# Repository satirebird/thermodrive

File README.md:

# Thermal actuator driver for homematic HmIP-MOD-OC8

This PCB controls up to 6 thermal actuators (230VAC) using a homematic [HmIP-MOD-OC8](https://de.elv.com/elv-homematic-ip-komplettbausatz-modulplatine-opencollector-8-fach-hmip-mod-oc8-fuer-smart-home-hausautomation-150850) module. To control the actuators solid state relays with FETs are used. TRIACs are problematic due to the minimum hold current. The board fits into the DIN rail case [APRA DB6 GBK](https://www.apra.de/produkte/apra-rail-db-serie/)

Schematic, Layout and Gerber files can be used without any warranties.

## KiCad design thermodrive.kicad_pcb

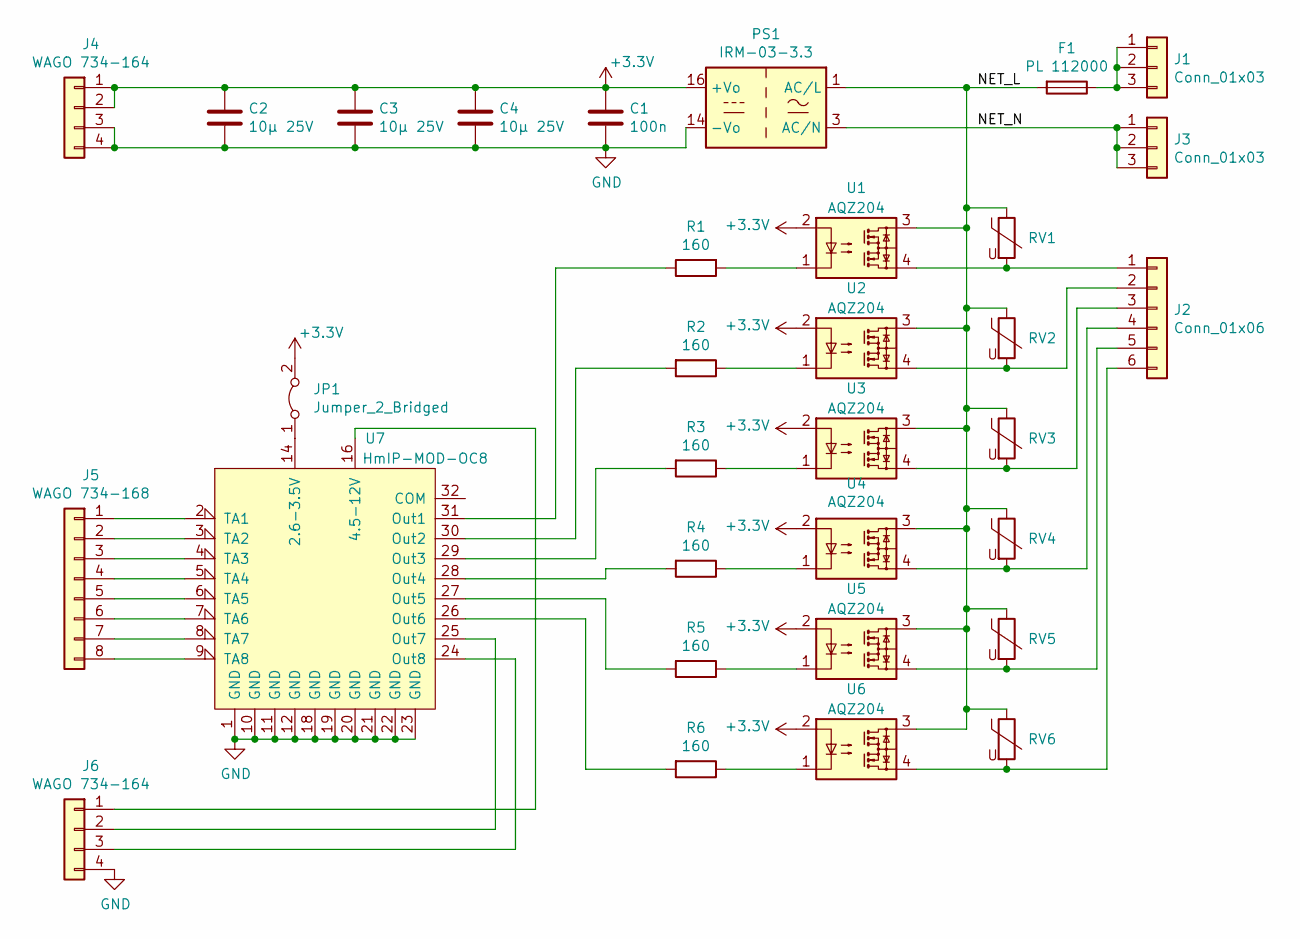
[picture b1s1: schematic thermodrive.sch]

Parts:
C1: 100n; C_0805_2012Metric
C2, C3, C4: 10µ 25V; C_1206_3216Metric
F1: PL 112000; Fuseholder5x20_horiz_SemiClosed_Casing10x25mm
J1, J3: Conn_01x03; TerminalBlock_MetzConnect_Type175_RT02703HBLC_1x03_P7.50mm_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
J2: Conn_01x06; TerminalBlock_MetzConnect_Type175_RT02706HBLC_1x06_P7.50mm_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
J4, J6: WAGO 734-164; Wago_734-164_1x04_P3.50mm_Horizontal
J5: WAGO 734-168; Wago_734-168_1x08_P3.50mm_Horizontal
JP1: Jumper_2_Bridged; PinHeader_1x02_P2.54mm_Vertical
PS1: IRM-03-3.3; Converter_ACDC_MeanWell_IRM-03-xx_THT
R1, R2, R3, R4, R5, R6: 160; R_0805_2012Metric
RV1, RV2, RV3, RV4, RV5, RV6: B72210P2271K101; RV_Disc_D12mm_W3.9mm_P7.5mm
U1, U2, U3, U4, U5, U6: AQZ204; AQZ-SIL-4
U7: HmIP-MOD-OC8

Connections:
+3V3: C1.1, C2.1, C3.1, C4.1, J4.1, J4.2, JP1.2 (B), PS1.16 (+Vo), U1.2, U2.2, U3.2, U4.2, U5.2, U6.2
/NET_L: F1.2, PS1.1 (AC/L), RV1.1, RV2.1, RV3.1, RV4.1, RV5.1, RV6.1, U1.3, U2.3, U3.3, U4.3, U5.3, U6.3
/NET_N: J3.1, J3.2, J3.3, PS1.3 (AC/N)
GND: C1.2, C2.2, C3.2, C4.2, J4.3, J4.4, J6.4, PS1.14 (-Vo), U7.1 (GND), U7.10 (GND), U7.11 (GND), U7.12 (GND), U7.18 (GND), U7.19 (GND), U7.20 (GND), U7.21 (GND), U7.22 (GND), U7.23 (GND)
unnamed: F1.1, J1.1, J1.2, J1.3
unnamed: J2.1, RV1.2, U1.4
unnamed: J2.2, RV2.2, U2.4
unnamed: J2.3, RV3.2, U3.4
unnamed: J2.4, RV4.2, U4.4
unnamed: J2.5, RV5.2, U5.4
unnamed: J2.6, RV6.2, U6.4
unnamed: J5.1, U7.2 (TA1)
unnamed: J5.2, U7.3 (TA2)
unnamed: J5.3, U7.4 (TA3)
unnamed: J5.4, U7.5 (TA4)
unnamed: J5.5, U7.6 (TA5)
unnamed: J5.6, U7.7 (TA6)
unnamed: J5.7, U7.8 (TA7)
unnamed: J5.8, U7.9 (TA8)
unnamed: J6.1, U7.16 (4.5-12V)
unnamed: J6.2, U7.25 (Out7)
unnamed: J6.3, U7.24 (Out8)
unnamed: JP1.1 (A), U7.14 (2.6-3.5V)
unnamed: R1.1, U7.31 (Out1)
unnamed: R1.2, U1.1
unnamed: R2.1, U2.1
unnamed: R2.2, U7.30 (Out2)
unnamed: R3.1, U3.1
unnamed: R3.2, U7.29 (Out3)
unnamed: R4.1, U4.1
unnamed: R4.2, U7.28 (Out4)
unnamed: R5.1, U5.1
unnamed: R5.2, U7.27 (Out5)
unnamed: R6.1, U6.1
unnamed: R6.2, U7.26 (Out6)

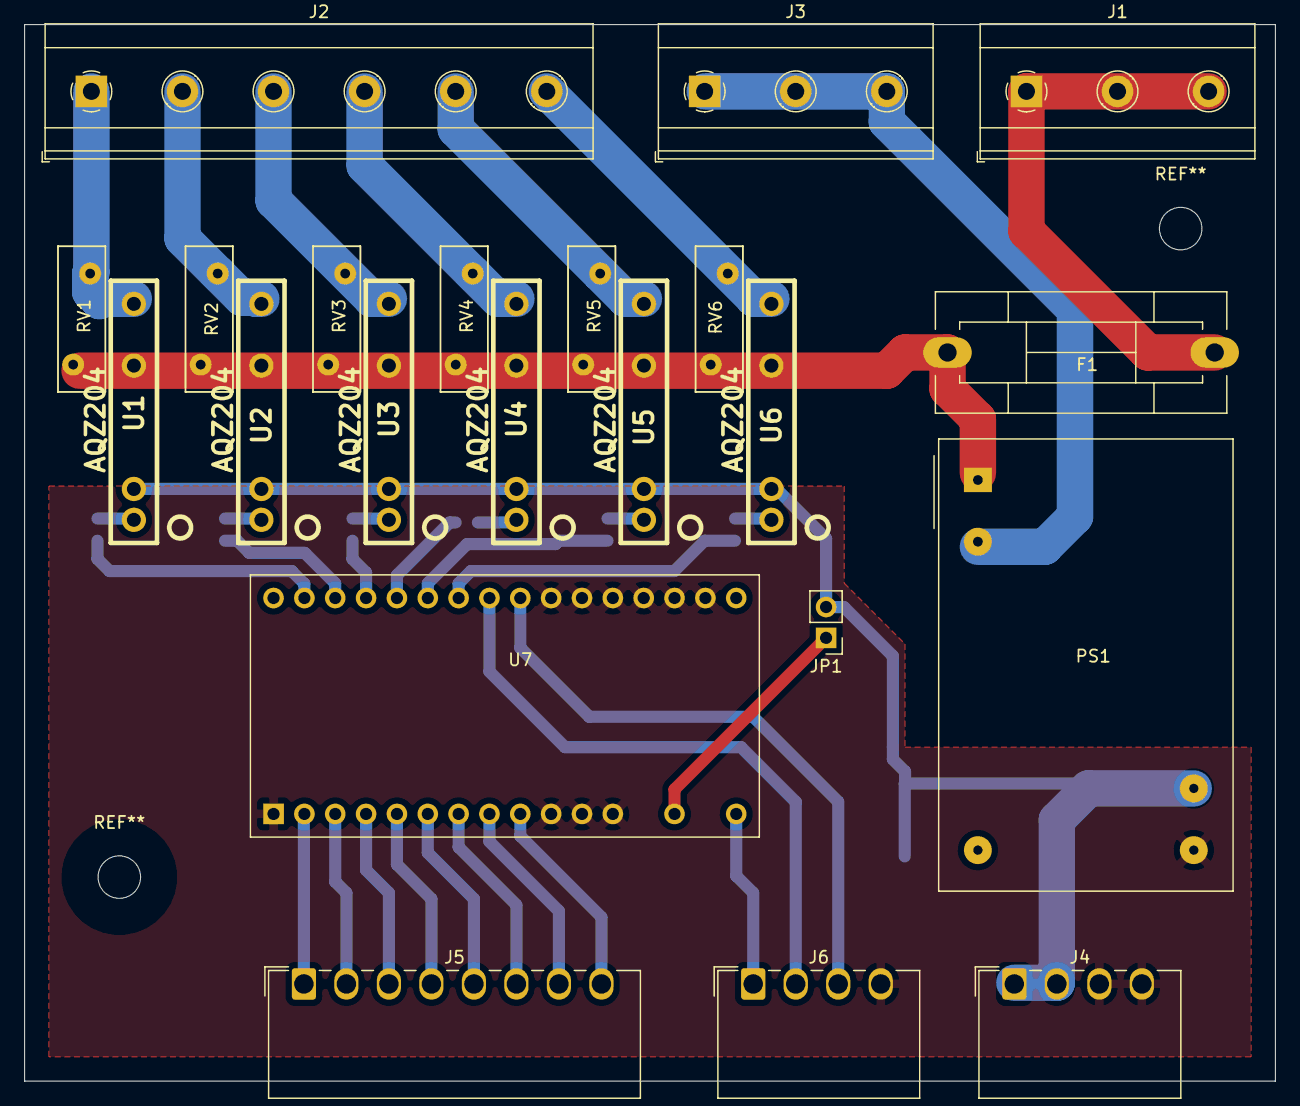
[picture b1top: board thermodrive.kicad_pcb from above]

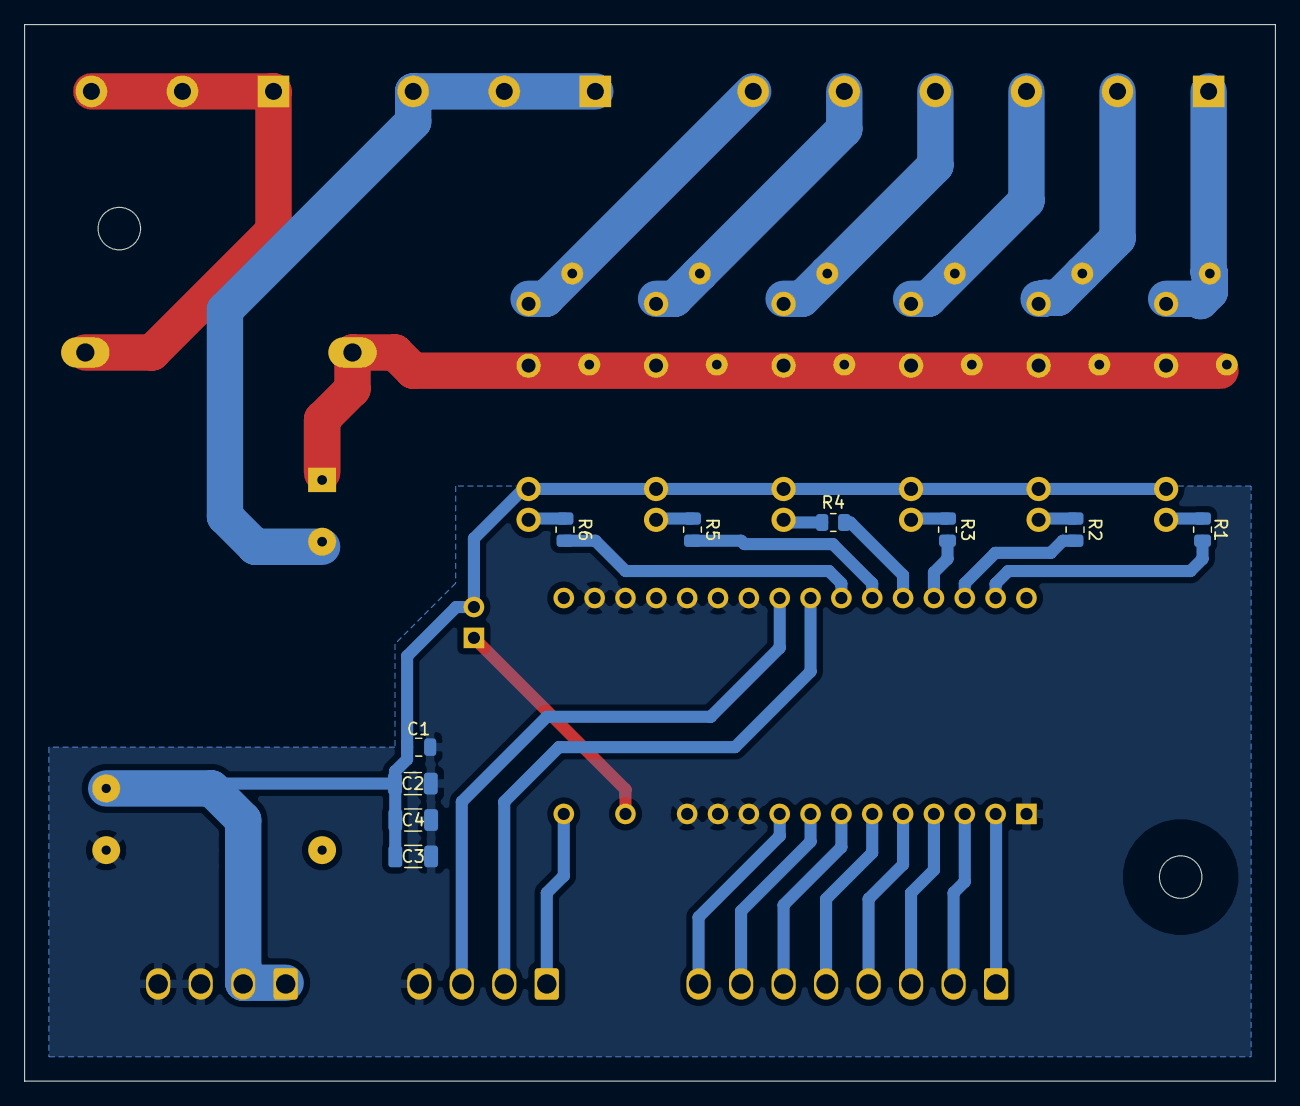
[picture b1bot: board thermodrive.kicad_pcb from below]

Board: 2 copper layers, 103.0 x 87.0 mm, 32 parts (10 on the bottom side), 35 nets.

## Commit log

2020-11-01 Add readme
2020-11-01 Add license file, pcb image
